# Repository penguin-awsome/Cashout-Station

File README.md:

# Cashout-Station

Hello everybody, this is my latest project: The Cashout Station!

This project is inspired from my favorite video game,'The Finals', a team based FPS shooter, as well as one of my friends projects: https://github.com/jamdotjar/ULTRATERM which is another terminal inspired from a video game. In the game, the cashout is the objective point, where you insert the 'Cashbox' to begin an objective point. In my version, you insert the cahbox to launch the game and play some of the game music.

It uses a NFC Detector to detect when the cashbox has been inserted via an NFC tag, and uses a servo motor to pull the box in and close the opening for th ebox as well. It is powered by a 9v battery being stepped down to 5v to run a Xiao ESP32-C6 which is the brains of the operation. It also includes some LEDs for flair and a speaker and mini amp for the sound. It also has two buttons, one for opening up the insertion slot and one for ejecting it.

Here are some photos of the finished design:

It's been really fun, albeit exausing working on this project due to a time crunch for submission time, but I'm so exited to actually build and use this thing! If you want to see the finished project, I'll be adding some photos and maybe a quick video here when completed hopefully before august 7th (The deadline)

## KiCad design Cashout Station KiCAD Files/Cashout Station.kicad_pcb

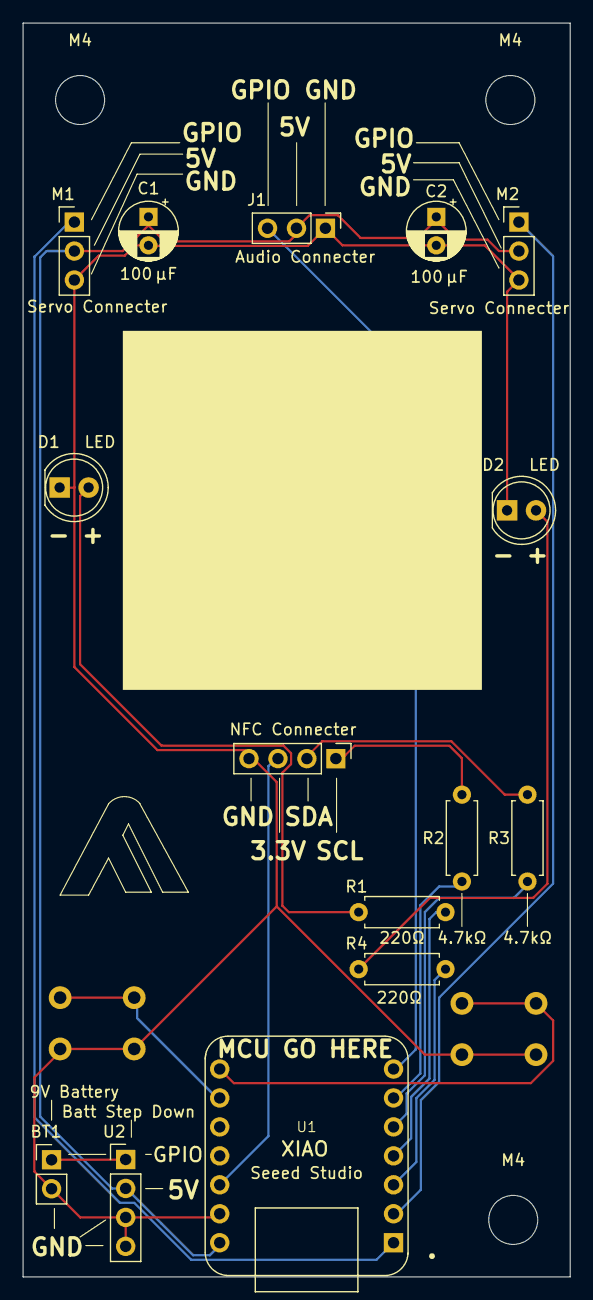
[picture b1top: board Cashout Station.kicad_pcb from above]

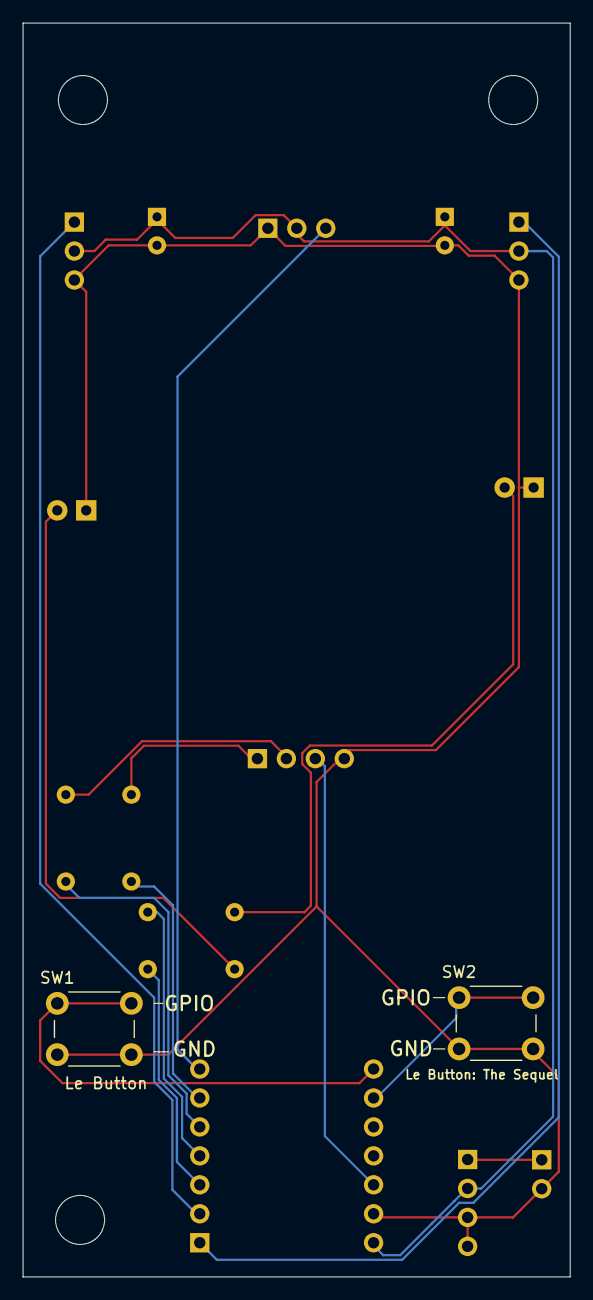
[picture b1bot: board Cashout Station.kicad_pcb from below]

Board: 2 copper layers, 48.0 x 110.0 mm, 20 parts (2 on the bottom side), 17 nets.

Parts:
BT1: 9V Battery; PinHeader_1x02_P2.54mm_Vertical
C1, C2: 100 µF; CP_Radial_D5.0mm_P2.50mm
D1, D2: LED; LED_D5.0mm
J1: Audio Connecter; PinHeader_1x03_P2.54mm_Vertical
M1, M2: Servo Connecter; PinHeader_1x03_P2.54mm_Vertical
M4, M4#2, M4#3: MountingHole_4.3mm_M4
NFC Connecter: PinHeader_1x04_P2.54mm_Vertical
R1, R4: 220Ω; R_Axial_DIN0207_L6.3mm_D2.5mm_P7.62mm_Horizontal
R2, R3: 4.7kΩ; R_Axial_DIN0207_L6.3mm_D2.5mm_P7.62mm_Horizontal
SW1: Le Button: The Sequel; SW_PUSH_6mm
SW2: Le Button; SW_PUSH_6mm
U1: XIAO-ESP32-C6; XIAO-Generic-Thruhole-14P-2.54-21X17.8MM
U2: Batt Step Down; PinHeader_1x04_P2.54mm_Vertical

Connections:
+3.3V: NFC Connecter.3 (VCC), U1.12 (3V3)
+5V: C1.1, C2.1, J1.2, M1.2 (+), M2.2 (+), U1.14 (VBUS), U2.2 (OUT+)
GND: BT1.2 (-), C1.2, C2.2, D1.1 (K), D2.1 (K), J1.1, M1.3 (-), M2.3 (-), NFC Connecter.4 (GND), SW1.2, SW2.2, U1.13 (GND), U2.3 (OUT-), U2.4 (VIN-)
unnamed: BT1.1 (+), U2.1 (VIN+)
unnamed: D1.2 (A), R1.1
unnamed: D2.2 (A), R4.1
unnamed: J1.3, U1.7 (GPIO16/D6/TX)
unnamed: M1.1 (PWM), U1.1 (GPIO0/A0/D0)
unnamed: M2.1 (PWM), U1.2 (GPIO1/A1/D1)
unnamed: NFC Connecter.1 (SCL), R2.2
unnamed: NFC Connecter.2 (SDA), R3.2
unnamed: R4.2, U1.3 (GPIO2/A2/D2)
unnamed: SW1.1, U1.8 (GPIO17/D7/RX)
unnamed: SW2.1, U1.9 (GPIO19/D8/SCK)
unnamed: R1.2, U1.4 (GPIO21/D3)
unnamed: R3.1, U1.5 (GPIO22/D4/SDA)
unnamed: R2.1, U1.6 (GPIO23/D5/SCL)

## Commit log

2025-07-17 Add KiCAD files back as regular folder
2025-07-22 Entry July 17th-22nd
2025-07-24 Created PCB
2025-07-27 PCB Updated, CAD almost complete
2025-07-28 Journal Entry July 23rd-27th
2025-07-28 Created BOM
2025-07-28 Wrote README.md
2025-07-28 Added Total Cost
2025-07-29 Added basic code inputs
2025-07-29 Added Drivers and Micropython
2025-07-29 Code Finished?
2025-07-29 Journal Entry June 28th-29th
2025-07-29 Added CAD Files
2025-07-29 Add .step
